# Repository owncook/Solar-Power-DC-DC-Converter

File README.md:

# Solar Powered DC Converter
## Circuits Design Project - EE2185 Project 2
👤 Owen Cook  
👤 Nate Seibold

## Motivation

The goal of the project was to design and build a prototype DC step down converter based on user specifications. The converter needed to run off of a 20V solar panel and be able to supply the user-defined voltage as an output. By nature, the circuit should also be able to adapt the pulse width to prevent solar panel voltage fluctuations from impacting the output. In addition to the previously listed requirements, the circuit should use minimal power and avoid overheating any components.

## Solution

To tackle the problem, the proposed design involves using an Arduino Micro attached to a PCB shield. This design utilizes a buck circuit and Arduino’s built-in PWM generator to cut the 20V output down to the desired output, in this case, 1.2V to power a DC motor. A custom PCB was designed to house the circuit elements, and once assembled, the Arduino fits onto the board to provide a compact and durable form factor. Although not included in the prototype design, the form factor enables easy attachment to a headband or other mounting solution.

The design is relatively inexpensive to produce, as the vast majority of its components cost less than a dollar. The two main expenses come from the shipping of the PCB and Arduino. Both of these costs would be lowered when production levels increased. Supply chain optimization would also aid in lowering costs as most of the PCB cost came from shipping expenses. Below is a brief breakdown of the costs associated with the prototype model, a full budget can be found in Appendix A.

| Item            | Price |
|----------------|-------|
| Arduino Micro  | $10.00|
| PCB+Shipping   | $20.00|
| Circuit Materials | $1.30|

The total price per unit is approximately $31.30, this leaves plenty of room in the budget for a mounting solution. As previously mentioned, these costs would likely continue to lower with more units made.

## Schedule

The timeframe for the project was set at 8 weeks, and the project finished ahead of schedule. Below is the planned timeline.

Most tasks were completed ahead of schedule during the design process. A working circuit was constructed in Week 2, the remaining time in Week 3 was used to diagnose some initial problems related to overheating components. After new component values were chosen, the circuit began to work as expected. PCB design was started during the initial testing weeks, in order to ensure an on-time delivery. The total PCB design and build process took roughly 4 weeks. In between ordering and receiving the PCB, code development took place. A working base code was produced in 1 week, and later weeks would be dedicated to refining the code to increase reaction time and stability. This process was expected to take the longest, but ended up being relatively straightforward. Upon the arrival of the PCB, the week-long final assembly process began and was completed without complications. The following weeks were spent conducting testing and producing reports.

## Results

After the 8 week development period, a working prototype was created that achieves all of the aforementioned goals. The prototype has been run off of a benchtop DC voltage source mimicking 20V from the sun, which worked as expected with no overheating. We then took it outside, connected it to a solar panel, and successfully powered the DC motor. A picture of the assembled prototype can be seen below.

The two screw terminals represent the input voltage and the output voltage. The longer wires are the output and the shorter wires are the input. We picked a pulse width and period so that the input would be let through to the output circuit just long enough to charge it up to the desired output voltage, then the switch was closed. This desired output kept adjusting itself based on the feedback voltage. The desired output can easily be chosen in the code.

## Validation

With the device running off of 20V from the DC power supply, the circuit draws about 0.18 A of current and 3.6 W of power. We tested other input voltages and saw that the power output stays relatively the same, decreasing slightly as the input voltage is decreased. We recorded the power and current draw based on different input voltages below:

| Input Voltage (V) | Current Draw (A) | Power (W) |
|--------------------|-------------------|-----------|
| 20                 | 0.180             | 3.60      |
| 17.5               | 0.187             | 3.27      |
| 15                 | 0.212             | 3.18      |
| 12.5               | 0.245             | 3.06      |
> _Current is estimated as it constantly changes due to PWM adjustments_

As seen above, as we decrease the voltage, the current increases. This is good for output purposes as the DC motor stays spinning as we decrease the input voltage. We found that it was best to keep the input voltage as specified, 20V, to limit the current and ultimately the heat production of the circuit components.

Shown above in yellow is an oscilloscope reading recording the voltage of the PWM from the Arduino, and in green, the output voltage across the load. This was tested with the desired output being 5V and as seen in the image, the output is hovering around 5V. We also measured with a multimeter and got a reading of 5V ±0.01V.

### Cost Breakdown

| Item               | Price |
|--------------------|-------|
| Arduino Micro      | $10.00|
| PCB (unit price at minimum quantity) | $2.00|
| Resistor (x5)      | $0.50 |
| Inductor (x3)      | $0.60 |
| NPN Transistor (2N3904) | $0.40 |
| Voltage Regulator (LM78L05) | $0.58 |
| FET (VP3203N3)     | $1.85 |
| Schottky Diode     | $0.43 |
| Capacitor          | $0.20 |

> The above prices were based on the purchase of one unit unless otherwise noted.

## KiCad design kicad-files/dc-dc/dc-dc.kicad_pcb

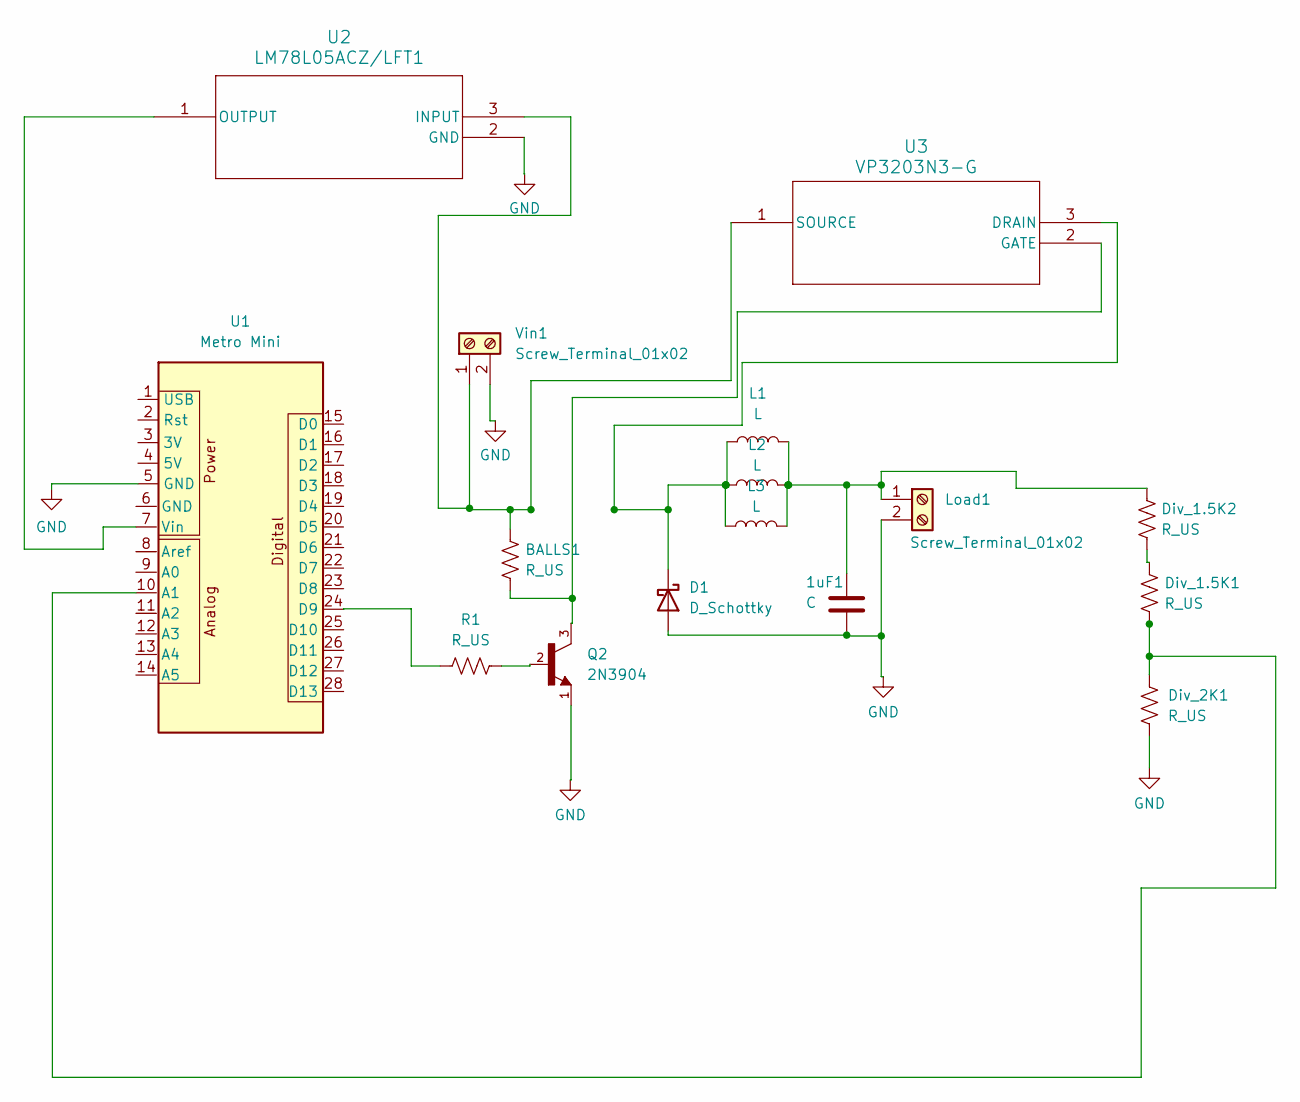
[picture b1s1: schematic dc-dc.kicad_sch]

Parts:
1uF1: C; C_Rect_L16.5mm_W13.9mm_P15.00mm_MKT
BALLS1: R_US; R_Axial_DIN0204_L3.6mm_D1.6mm_P5.08mm_Vertical
D1: D_Schottky; D_5W_P10.16mm_Horizontal
Div_1.5K1, Div_1.5K2: R_US; R_Axial_DIN0309_L9.0mm_D3.2mm_P12.70mm_Horizontal
Div_2K1: R_US; R_Axial_DIN0204_L3.6mm_D1.6mm_P5.08mm_Vertical
L1, L2, L3: L; L_Axial_L9.5mm_D4.0mm_P5.08mm_Vertical_Fastron_SMCC
Load1: Screw_Terminal_01x02; TerminalBlock_Altech_AK300-2_P5.00mm
Q2: 2N3904; PARTREV February 2003
R1: R_US; R_Axial_DIN0309_L9.0mm_D3.2mm_P12.70mm_Horizontal
U1: Metro Mini
U2: LM78L05ACZ/LFT1; LM78L05_voltage_regulator
U3: VP3203N3-G; VP3203
Vin1: Screw_Terminal_01x02; TerminalBlock_Altech_AK300-2_P5.00mm

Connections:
GND: 1uF1.2, D1.2 (A), Div_2K1.2, Load1.2, Q2.1, U1.5 (GND), U2.2 (GND), Vin1.2
unnamed: D1.1 (K), L1.1, L2.1, L3.1, U3.3 (DRAIN)
unnamed: Div_1.5K1.1, Div_1.5K2.2
unnamed: 1uF1.1, Div_1.5K2.1, L1.2, L2.2, L3.2, Load1.1
unnamed: Q2.2, R1.2
unnamed: Div_1.5K1.2, Div_2K1.1, U1.10 (A1)
unnamed: R1.1, U1.24 (D9)
unnamed: U1.7 (Vin), U2.1 (OUTPUT)
unnamed: BALLS1.1, U2.3 (INPUT), U3.1 (SOURCE), Vin1.1
unnamed: BALLS1.2, Q2.3, U3.2 (GATE)

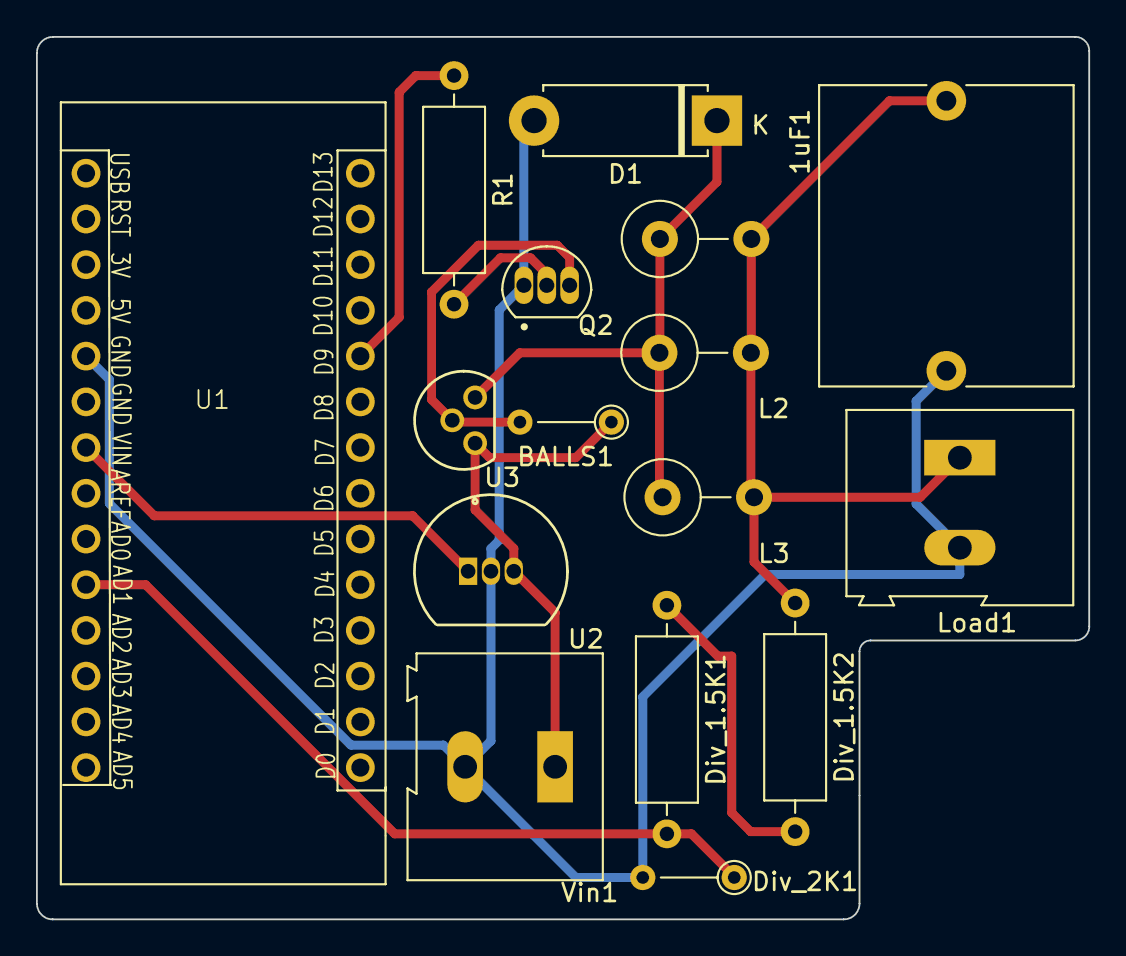
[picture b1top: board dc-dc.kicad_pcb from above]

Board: 2 copper layers, 58.5 x 49.0 mm, 16 parts (0 on the bottom side), 10 nets.

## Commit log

2024-04-25 added all files
2024-04-25 put DS_Store in the ignore file
2024-04-25 remove ds_store
2024-04-25 removed DS_Store from every path
